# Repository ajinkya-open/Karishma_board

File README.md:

# Karishma_board
This is open electronics project including Atmega328P,256 Kbytes of memory, and others
its open source electonics

Methos:
Download/clone this project
Make a folder <New_folder>
copy downloaded contents in this folder
Configure Kicad Download from :kicad-pcb.org/
open this project in Kicad
Ready to work

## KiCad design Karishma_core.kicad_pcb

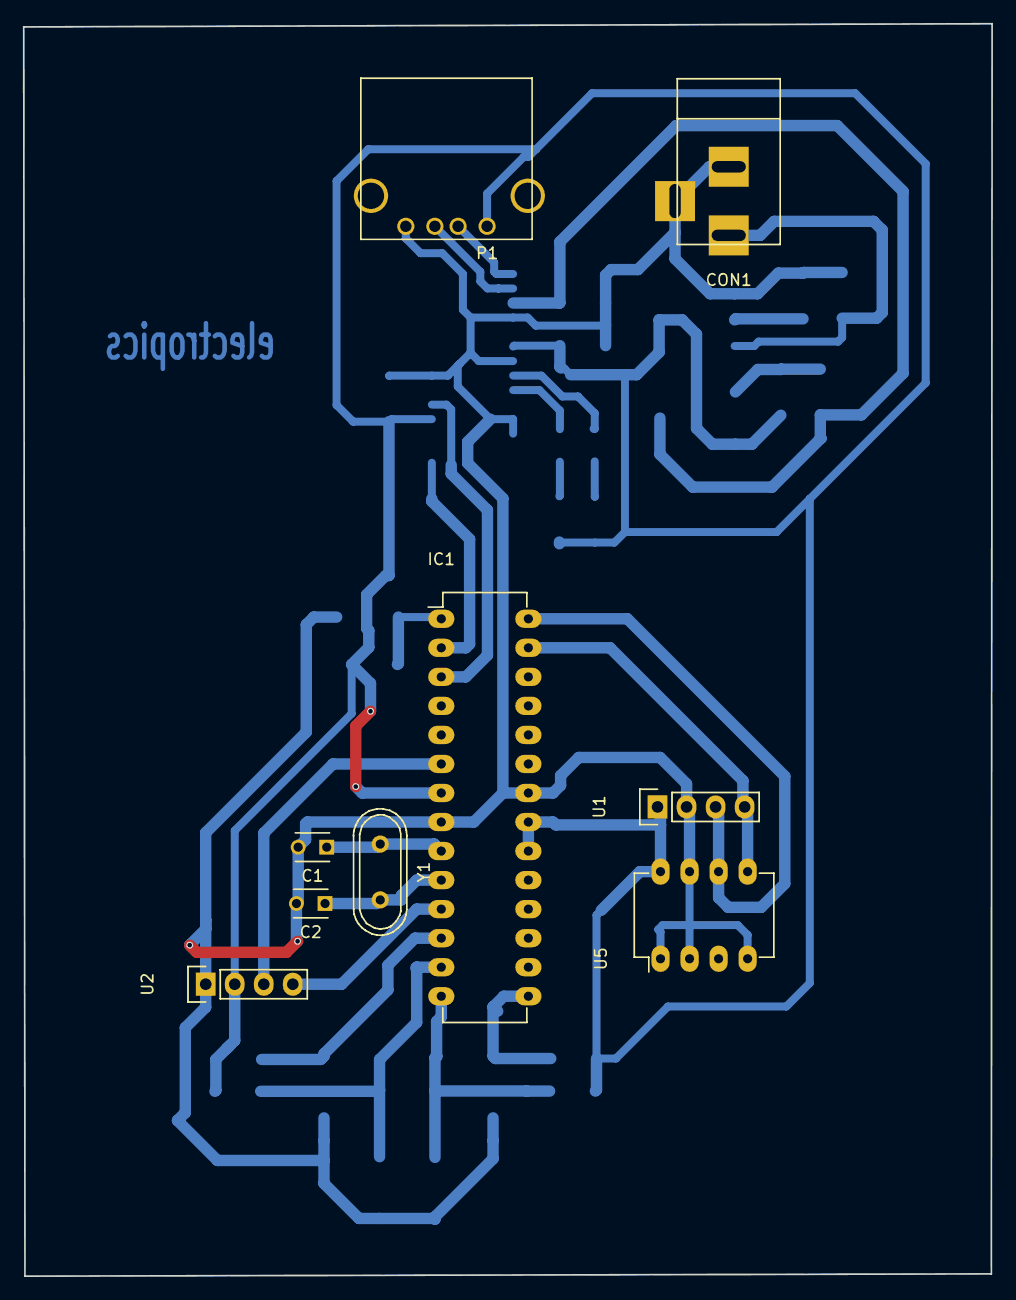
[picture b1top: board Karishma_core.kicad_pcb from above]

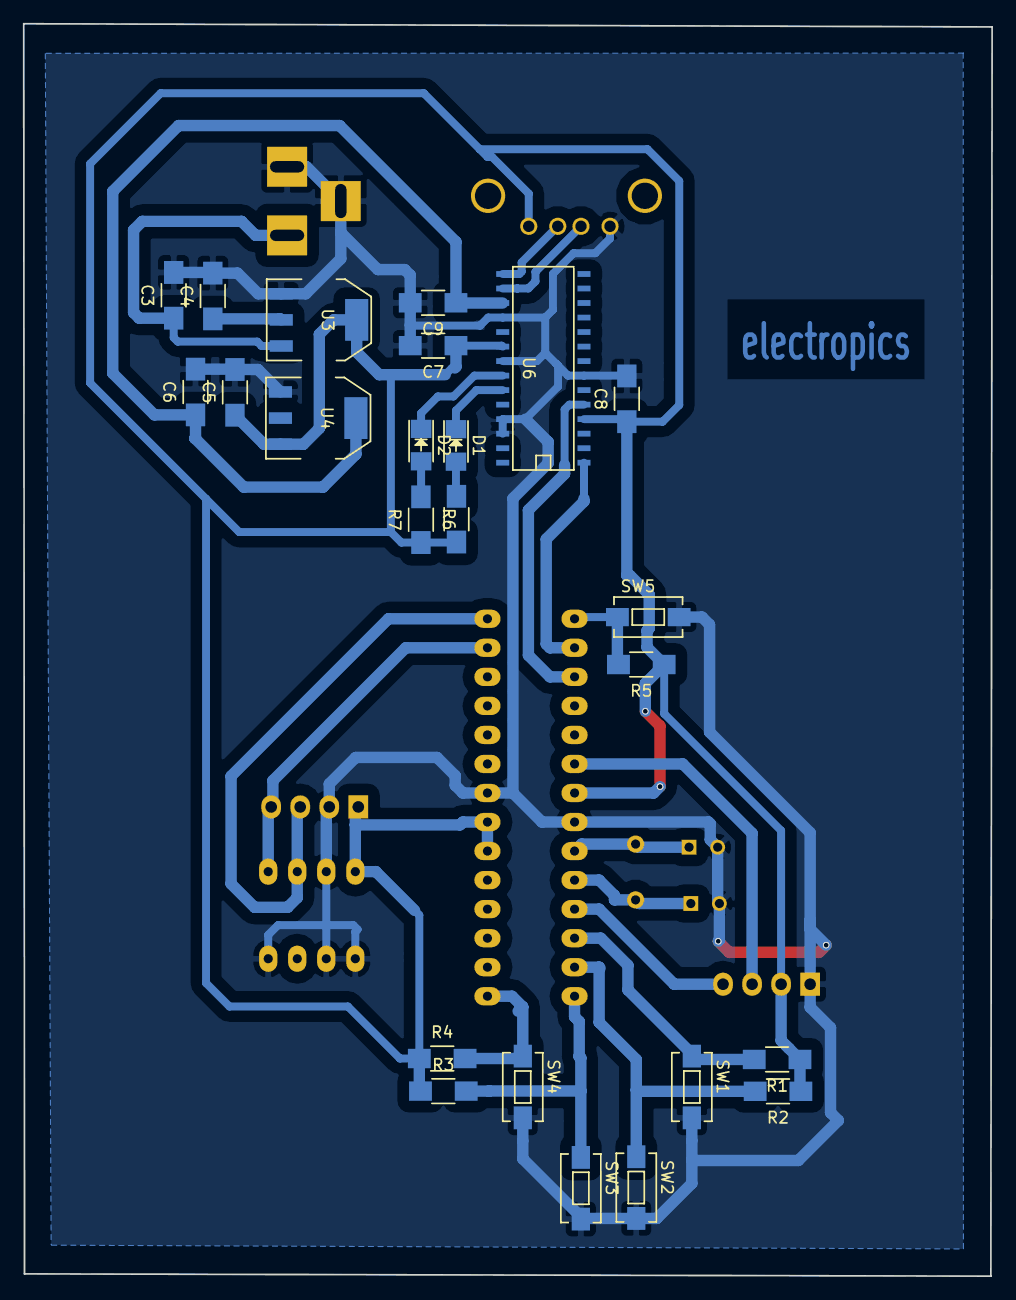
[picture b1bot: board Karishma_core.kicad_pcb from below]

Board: 2 copper layers, 84.7 x 109.6 mm, 33 parts (24 on the bottom side), 23 nets.

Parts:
C1, C2: 22pF; C_Disc_D3_P2.5
C3, C5: 100uF; R_1206_HandSoldering
C4, C6: 22uF; R_1206_HandSoldering
C7, C9: 0.1uF; R_1206_HandSoldering
C8: 10uF; R_1206_HandSoldering
CON1: BARREL_JACK
D1: TxLED; LED_1206
D2: RxLED; LED_1206
IC1: ATMEGA328-P; DIP-28_W7.62mm_LongPads
P1: USB_A
R1, R2, R3, R4, R5: 4.7K; R_1206_HandSoldering
R6, R7: 1K; R_1206_HandSoldering
SW1, SW2, SW3, SW4, SW5: SW_PUSH; SW_SPST_EVQPE1
U1: OledDisplay; Pin_Header_Straight_1x04
U2: FingerPrintSensor; Pin_Header_Straight_1x04
U3: AMS1117_5V; SOT-223_modified
U4: AMS1117_3.3V; SOT-223_modified
U5: I2CMemoty24LS256; DIP-8_W7.62mm_LongPads
U6: FTDI232RL; SOIC-28
Y1: 16MHz; Crystal_HC49-U_Vertical

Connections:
3.3V: C6.1, C9.1, U4.2, U6.17
5V: C4.1, C5.1, C7.1, C8.1, IC1.7, IC1.20, IC1.21, P1.1, R1.1, R2.1, R3.1, R4.1, R5.1, R6.1, R7.1, U1.1, U2.2, U3.2, U4.3, U5.8, U6.4, U6.20
/ControllerSheet/R_F: IC1.11, U2.4
/ControllerSheet/SCL: IC1.28, U1.3, U5.6
/ControllerSheet/SDA: IC1.27, U1.4, U5.5
/ControllerSheet/T_F: IC1.6, U2.3
D+: P1.3, U6.16
D-: P1.2, U6.15
GND: C1.2, C2.2, C3.2, C4.2, C5.2, C6.2, C7.2, C8.2, C9.2, CON1.2, CON1.3, IC1.8, IC1.22, P1.4, SW1.2, SW2.2, SW3.2, SW4.2, SW5.2, U1.2, U2.1, U3.1, U4.1, U5.1, U5.2, U5.4, U5.7, U6.7, U6.18, U6.21, U6.25, U6.26
unnamed: C3.1, CON1.1, U3.3
unnamed: D1.1, U6.23
unnamed: D1.2, R6.2
unnamed: D2.1, U6.22
unnamed: D2.2, R7.2
Push1: IC1.12, R1.2, SW1.1
Push2: IC1.13, R2.2, SW2.1
Push3: IC1.14, R3.2, SW3.1
Push4: IC1.15, R4.2, SW4.1
RXD: IC1.3, U6.5
Reset: IC1.1, R5.2, SW5.1
TXD: IC1.2, U6.1
Xtal1: C1.1, IC1.9, Y1.1
Xtal2: C2.1, IC1.10, Y1.2
